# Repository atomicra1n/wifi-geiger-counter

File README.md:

# Wi-Fi Geiger Counter

A DIY Geiger counter PCB which can detect ionizing radiation and log readings over Wi-Fi. Built with a Raspberry Pi Pico 2 W, and a HV multiplier circuit that steps up 3.7V to 400V for the GM tube. Made THT to be easily buildable.

## Features

- M4011/SBM-20 Geiger tube with pulse detection (tuned for M4011)
- Custom HV circuit (around 400V) with a single LiPo cell
- Wi-Fi data logging with a dashboard and a JSON API
- Piezo buzzer with clicking on each count
- Battery charging via the Pico's Micro-USB port
- Power switch
- Fully THT with parts from my local electronic shop (GM Electronic)

## Motivation
I made this project as I already own a FNIRSI GC-01 Geiger Counter, but I've always been intrigued by how they work and wanted to have a crack at making my own. It was an interesting challenge, especially given the difficulties around handling 400 volts, clearance, etc. Additionally, given the addition of Wi-Fi compared to the GC-01, I can log data from anywhere (the GC-01 requires a constant USB-C connection).

## Functionality
- Power from the Pico's Micro-USB goes through the VBUS to a TP4056 charger module which charges the battery. 
- Pico uses PWM on a MPSA42 transistor which switches an inductor, it ramps up to 200V-ish and then a diode + capacitor voltage doubler ups that to around 400V.
- A 40Megaohm/220kiloohm resistor divider reduces the 400V down to around 2.19, which is read by the Pico via its ADC and PID in the firmware adjusts to continuously hold at 400V.
- When the M4011 tube detects decay, the pulse enters a transistor and it is turned into a 3.3V signal for the Pico which is counted and clicks the buzzer.
- The firmware tallies counts over 60 seconds to calculate a CPM and converts into micro Sv/h via the configured conversion factor. Pico hosts a small web page and a JSON endpoint.

## How it was made
This is my first project in KiCad, so I had to figure it out for the most part. I picked the parts on LCSC and imported them, sketched the HV circuit on paper and then built it step by step. A few issues I ran into:
- I configured net class patterns to keep HV clearance, but I misconfigured them (set to HV instead of /HV) and they were ignored. As such, when I thought I was done, none of my rules were actually checked.
- My USB TVS diode was wired the wrong way which would short VBUS. I swapped it for a bidirectional one.
- My status LED was backwards and improperly wired, so I changed it to stay high on boot.
- The USB-C connector was facing inside the board instead of outside, very easy mistake to make in the PCB editor! Had to rotate and reroute completely.
- The buzzer footprint didn't match my actual part, so I had to find the right one on LCSC and reimport it.
- The ADC reading was wrong by around 30% in the firmware, so I fixed it by using the calibrated ADC reading in MicroPython

### v2 (THT)
After my project got approved, I realized it was practically unbuildable, as the ESP32 had pads underneath and everything was tiny SMD, which for a beginner solderer like me was straight up impossible. As I had no hot air or hot plate (I only have a Pinecil), I redesigned it to be THT from my local retailer, which even saved some costs.

## Tech stack
- KiCad for the PCB design
- MicroPython for the Pico firmware
- JLCPCB for the board and GM Electronic for parts

## Repo layout
- pcb/ contains the actual KiCad project
- pcb/gerbers contain the gerber and drill files
- pcb/lib/ contains my custom footprints
- firmware/ contains the MicroPython code
- images/ contains a render of the PCB and other images
- BOM.csv contains the parts list
- JOURNAL.md is the devlog

## Bill of materials

| Part | Qty | Source | Unit | Total |
|---|---|---|---|---|
| [PCB Manufacturing](https://jlcpcb.com) | 1 | JLCPCB | $4.00 | $4.00 |
| [RASPBERRY Pico 2 WH](https://www.gme.cz/v/1517388/raspberry-pico-2-wh) | 1 | GM Electronic | $11.97 | $11.97 |
| [CONNFLY BL120G-V8.5 female header 1x20pin](https://www.gme.cz/v/1498892/connfly-bl120g-v85-dutinkova-lista-1x20pin-roztec-254mm-vyska-85mm) | 2 | GM Electronic | $0.44 | $0.88 |
| [CREATALL CA-033M TP4056 charger module](https://www.gme.cz/v/1518943/creatall-ca-033m-nabijecka-li-ion-clanku-tp4056-s-ochranou-microusb) | 1 | GM Electronic | $0.88 | $0.88 |
| [SEMTECH MPSA42 transistor](https://www.gme.cz/v/1485978/semtech-mpsa42-b-p-bipolarni-tranzistor) | 8 | GM Electronic | $0.13 | $1.04 |
| [FASTRON 09P-103J inductor 10mH](https://www.gme.cz/v/1487059/fastron-09p-103j-tlumivka) | 1 | GM Electronic | $0.91 | $0.91 |
| [HER108 diode](https://www.gme.cz/v/1493669/her108-dioda) | 12 | GM Electronic | $0.09 | $1.08 |
| [WIMA MKS4 10n/1500V](https://www.gme.cz/v/1491351/wima-mks4-10n-1500v-k-rm15-foliovy-kondenzator) | 3 | GM Electronic | $0.67 | $2.01 |
| [1N5819 Schottky](https://www.gme.cz/v/1493662/1n5819-schottkyho-dioda) | 6 | GM Electronic | $0.14 | $0.84 |
| [Resistor 1 kiloohm 0207](https://www.gme.cz/v/1486228/gym-cym-rm-1k-06w-1-0207-metalizovany-rezistor) | 10 | GM Electronic | $0.10 | $1.00 |
| [Resistor 10 kiloohm 0207](https://www.gme.cz/v/1494150/gym-cym-rm-10k-06w-1-0207-metalizovany-rezistor) | 10 | GM Electronic | $0.10 | $1.00 |
| [Resistor 100 kiloohm 0207](https://www.gme.cz/v/1494147/gym-cym-rm-100k-06w-1-0207-metalizovany-rezistor) | 10 | GM Electronic | $0.10 | $1.00 |
| [Resistor 220 kiloohm 0207](https://www.gme.cz/v/1493098/gym-cym-rm-220k-06w-1-0207-metalizovany-rezistor) | 10 | GM Electronic | $0.10 | $1.00 |
| [Resistor 4.7 megaohm 0207](https://www.gme.cz/v/1493090/gym-cym-rm-4m7-06w-1-0207-metalizovany-rezistor) | 10 | GM Electronic | $0.10 | $1.00 |
| [Resistor 10 megaohm 0207](https://www.gme.cz/v/1494151/gym-cym-rm-10m-06w-1-0207-metalizovany-rezistor) | 10 | GM Electronic | $0.10 | $1.00 |
| [GYM/CYM CK 100n/63V](https://www.gme.cz/v/1489722/gym-cym-ck-100n-63v-x7r-rm508-20-keramicky-kondenzator) | 4 | GM Electronic | $0.18 | $0.72 |
| [HITANO CE 220u/16V 8x12](https://www.gme.cz/v/1485860/hitano-ce-220u-16vit-hit-exr-8x12-rm35-bulk-elektrolyticky-kondenzator) | 5 | GM Electronic | $0.15 | $0.75 |
| [BRIGHT LED BL-B5141-L red](https://www.gme.cz/v/1492965/bright-led-bl-b5141-l-led-3mm-cervena) | 1 | GM Electronic | $0.17 | $0.17 |
| [HITPOINT PT-2040PQ piezo](https://www.gme.cz/v/1496868/hitpoint-pt-2040pq-piezomenic) | 1 | GM Electronic | $0.84 | $0.84 |
| [MTS-102-A2 toggle](https://www.gme.cz/v/1501004/mts-102-a2-packovy-spinac) | 1 | GM Electronic | $0.65 | $0.65 |
| [JST PH 2pin header](https://www.gme.cz/v/1517850/jst-ph-20mm-2pin-konektor-na-dps) | 2 | GM Electronic | $0.11 | $0.22 |
| [JST PH 3pin cable](https://www.gme.cz/v/1517846/jst-ph-20mm-3pin-samice) | 2 | GM Electronic | $0.37 | $0.74 |
| [KSS KDA6M3X15W standoff](https://www.gme.cz/v/1483417/kss-kda6m3x15w-polyamid-bily-distancni-sloupek-15mm-m3-matka-sroub) | 4 | GM Electronic | $0.23 | $0.92 |
| [WURTH SKM3K nut M3](https://www.gme.cz/v/1511808/wurth-skm3k-matice-m3) | 4 | GM Electronic | $0.03 | $0.12 |
| [KSS CV-100 zip tie](https://www.gme.cz/v/1512662/kss-cv-100-stahovaci-pasek) | 8 | GM Electronic | $0.03 | $0.24 |
| [GM Tube - M4011](https://github.com/SensorsIot/Geiger-Counter-RadiationD-v1.1-CAJOE-/blob/master/M4011%20Geiger%20Tube%20Specification.pdf) | 1 | Salvaged (FNIRSI GC-01) | $0.01 | $0.01 |
| 3.7V LiPo battery | 1 | Salvaged (FNIRSI GC-01) | $0.01 | $0.01 |
| **Parts subtotal** | | | | **$35.00** |
| Shipping (estimate) | | | | $11.00 |
| **Total** | | | | **$46.00** |

The Geiger Tube and Battery were salvaged from my GC-01, so they're effectively free. You can buy similar pieces on Ebay, Aliexpress or other stores.

## Assembly
Please keep in mind the board makes around 400V, even though it's low current, it could still inflict a shock, as such, please be careful. Before touching the HV side, I recommend unplugging the USB and battery and shorting C10 to GND to discharge it.

1. Order the PCB from JLCPCB using the gerber files and the parts from GM using the BOM.
2. Start with the power section. Put a piece of electrical tape where the TP4056 module goes, zip tie the module on and wire its 6 pads to J2 following the silkscreen labels. Then solder D1, C1 (polarity!), C2, SW1 and the J1 battery connector. Check battery polarity before plugging in or you might kill it! If you turn on SW1, you should get the battery voltage (4Vish) on VSYS.
3. Solder the Pico sockets, led + R30, buzzer. Plug in the RPi with the usb port facing the left edge of the PCB. Flash Micropython.
4. Begin the HV supply. Solder Q1, R10, R11, L1, D3-D5, C8-C10, divider chain R13-R16, R12, C11, R23. Do not connect the tube yet. Run the firmware and see how much HV you get. Do not measure with a multimeter to avoid loading the circuit.
5. Now for the pulse detection, solder Q2, R24, R25 and R26.
6. To finish, zip tie your tube onto J3 and solder leads. VERIFY ANODE AND CATHODE! Screw in the four standoffs and connect the battery.

## Firmware

1. Start by downloading MicroPython for the Pico 2 W from [micropython.org](https://micropython.org/download/RPI_PICO2_W/). Hold the BOOTSEL button on the Pico while plugging in and drag the .uf2 onto the drive that shows up.
2. Fill in firmware/config.py.
3. Copy over files: config.py, geiger.py, hv_control.py, buzzer.py, wifi_manager.py, main.py.
4. If all goes well, your IP address should get printed over serial. Try opening it in the browser for the dashboard, or use /api/data for the JSON data.

## AI disclosure
LLMs (Claude Opus 4.6/5.5) was mostly used to get feedback on the schematic, review parts of it, assist in fixing bugs and writing the dashboard in wifi_manager.py. It was also used for other tedious but simple tasks, such as adding the BOM to this README.

---

Built for [Hack Club Half Life](https://halflife.hackclub.com/) 
Week 1 (PCBs).

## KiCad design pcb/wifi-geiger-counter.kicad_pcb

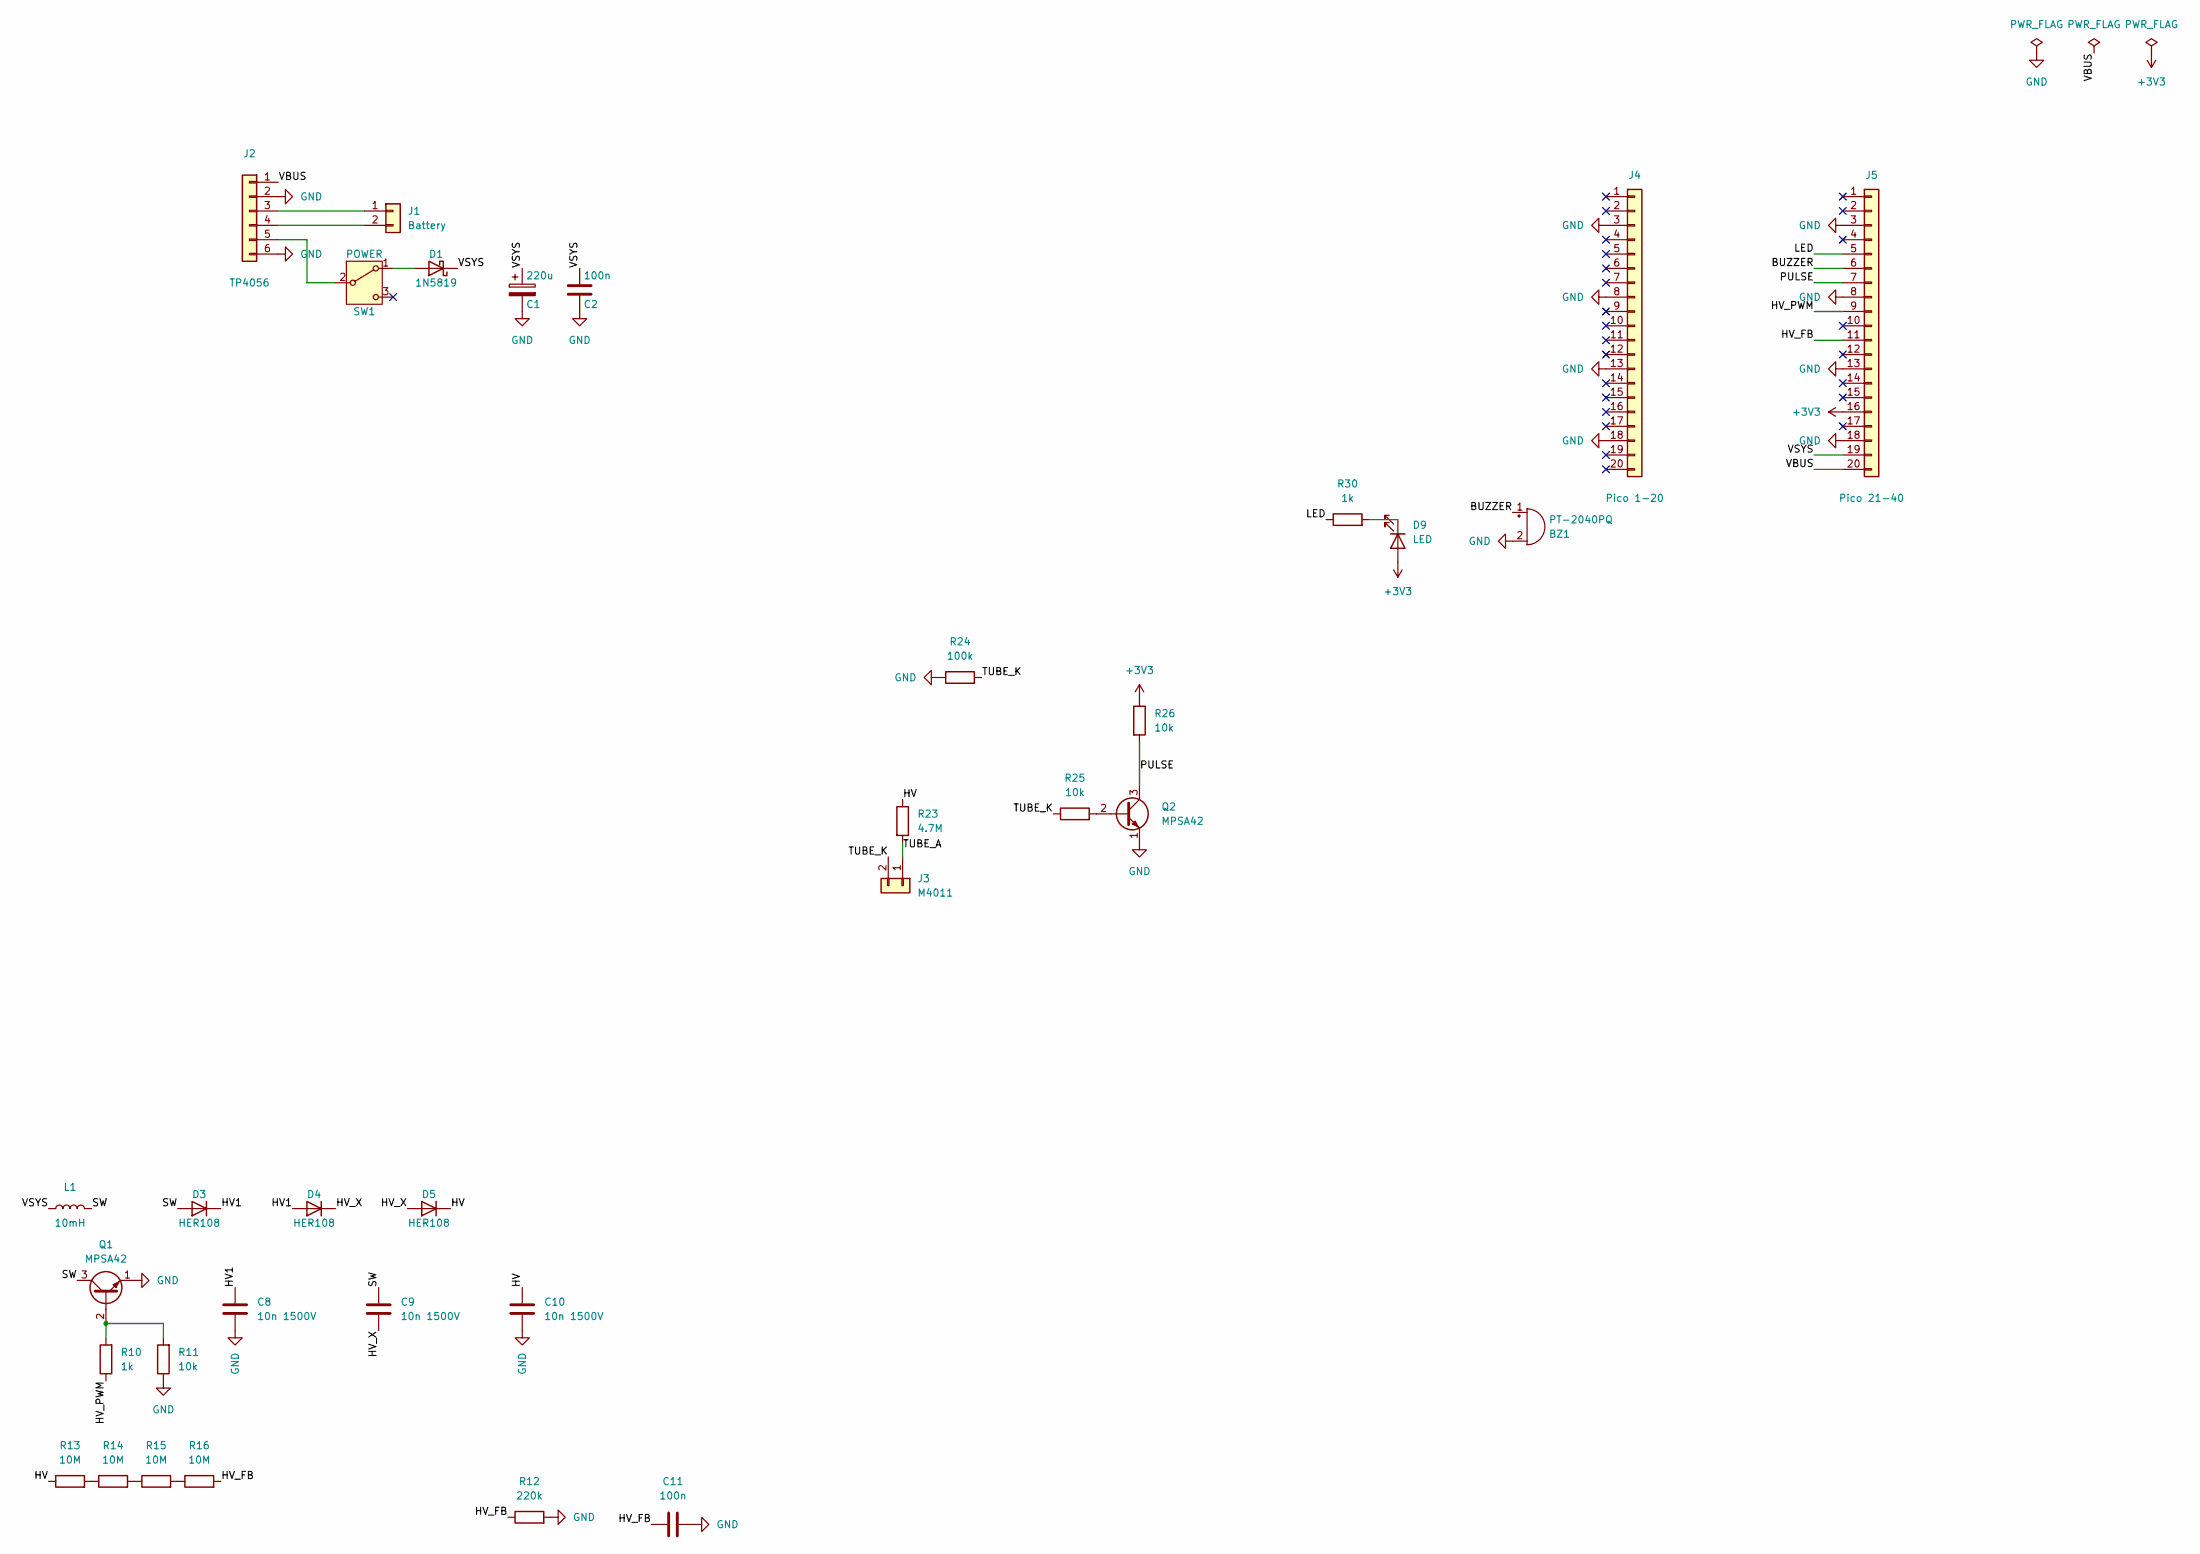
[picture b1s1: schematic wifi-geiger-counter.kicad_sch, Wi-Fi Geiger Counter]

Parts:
BZ1: PT-2040PQ; buzzer_2040pq
C1: 220u; CP_Radial_D8.0mm_P3.50mm
C2, C11: 100n; C_Disc_D5.0mm_W2.5mm_P5.00mm
C8, C9, C10: 10n 1500V; C_Rect_L18.0mm_W5.0mm_P15.00mm_FKS3_FKP3
D1: 1N5819; D_DO-41_SOD81_P10.16mm_Horizontal
D3, D4, D5: HER108; D_DO-41_SOD81_P10.16mm_Horizontal
D9: LED; LED_D3.0mm
J1: Battery; JST_PH_B2B-PH-K_1x02_P2.00mm_Vertical
J2: TP4056
J3: M4011; tube
J4: Pico 1-20; PinSocket_1x20_P2.54mm_Vertical
J5: Pico 21-40; PinSocket_1x20_P2.54mm_Vertical
L1: 10mH; L_Radial_D10.0mm_P5.00mm_Fastron_07P
Q1, Q2: MPSA42; TO-92_Inline_Wide
R10, R30: 1k; R_Axial_DIN0207_L6.3mm_D2.5mm_P10.16mm_Horizontal
R11, R25, R26: 10k; R_Axial_DIN0207_L6.3mm_D2.5mm_P10.16mm_Horizontal
R12: 220k; R_Axial_DIN0207_L6.3mm_D2.5mm_P10.16mm_Horizontal
R13, R14, R15, R16: 10M; R_Axial_DIN0207_L6.3mm_D2.5mm_P10.16mm_Horizontal
R23: 4.7M; R_Axial_DIN0207_L6.3mm_D2.5mm_P10.16mm_Horizontal
R24: 100k; R_Axial_DIN0207_L6.3mm_D2.5mm_P10.16mm_Horizontal
SW1: POWER; SW_MTS-102-A2

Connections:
+3V3: D9.2 (A), J5.16, R26.1
/BUZZER: BZ1.1 (+), J5.6
/HV: C10.1, D5.1 (K), R13.1, R23.1
/HV1: C8.1, D3.1 (K), D4.2 (A)
/HV_FB: C11.1, J5.11, R12.1, R16.2
/HV_PWM: J5.9, R10.1
/HV_X: C9.2, D4.1 (K), D5.2 (A)
/LED: J5.5, R30.1
/PULSE: J5.7, Q2.3 (C), R26.2
/SW: C9.1, D3.2 (A), L1.2, Q1.3 (C)
/TUBE_A: J3.1, R23.2
/TUBE_K: J3.2, R24.2, R25.1
/VBUS: J2.1, J5.20
/VSYS: C1.1, C2.1, D1.1 (K), J5.19, L1.1
GND: BZ1.2 (-), C1.2, C2.2, C8.2, C10.2, C11.2, J2.2, J2.6, J4.3, J4.8, J4.13, J4.18, J5.3, J5.8, J5.13, J5.18, Q1.1 (E), Q2.1 (E), R11.1, R12.2, R24.1
unnamed: D1.2 (A), SW1.1 (A)
unnamed: D9.1 (K), R30.2
unnamed: J1.1, J2.3
unnamed: J1.2, J2.4
unnamed: J2.5, SW1.2 (B)
unnamed: Q1.2 (B), R10.2, R11.2
unnamed: Q2.2 (B), R25.2
unnamed: R13.2, R14.1
unnamed: R14.2, R15.1
unnamed: R15.2, R16.1

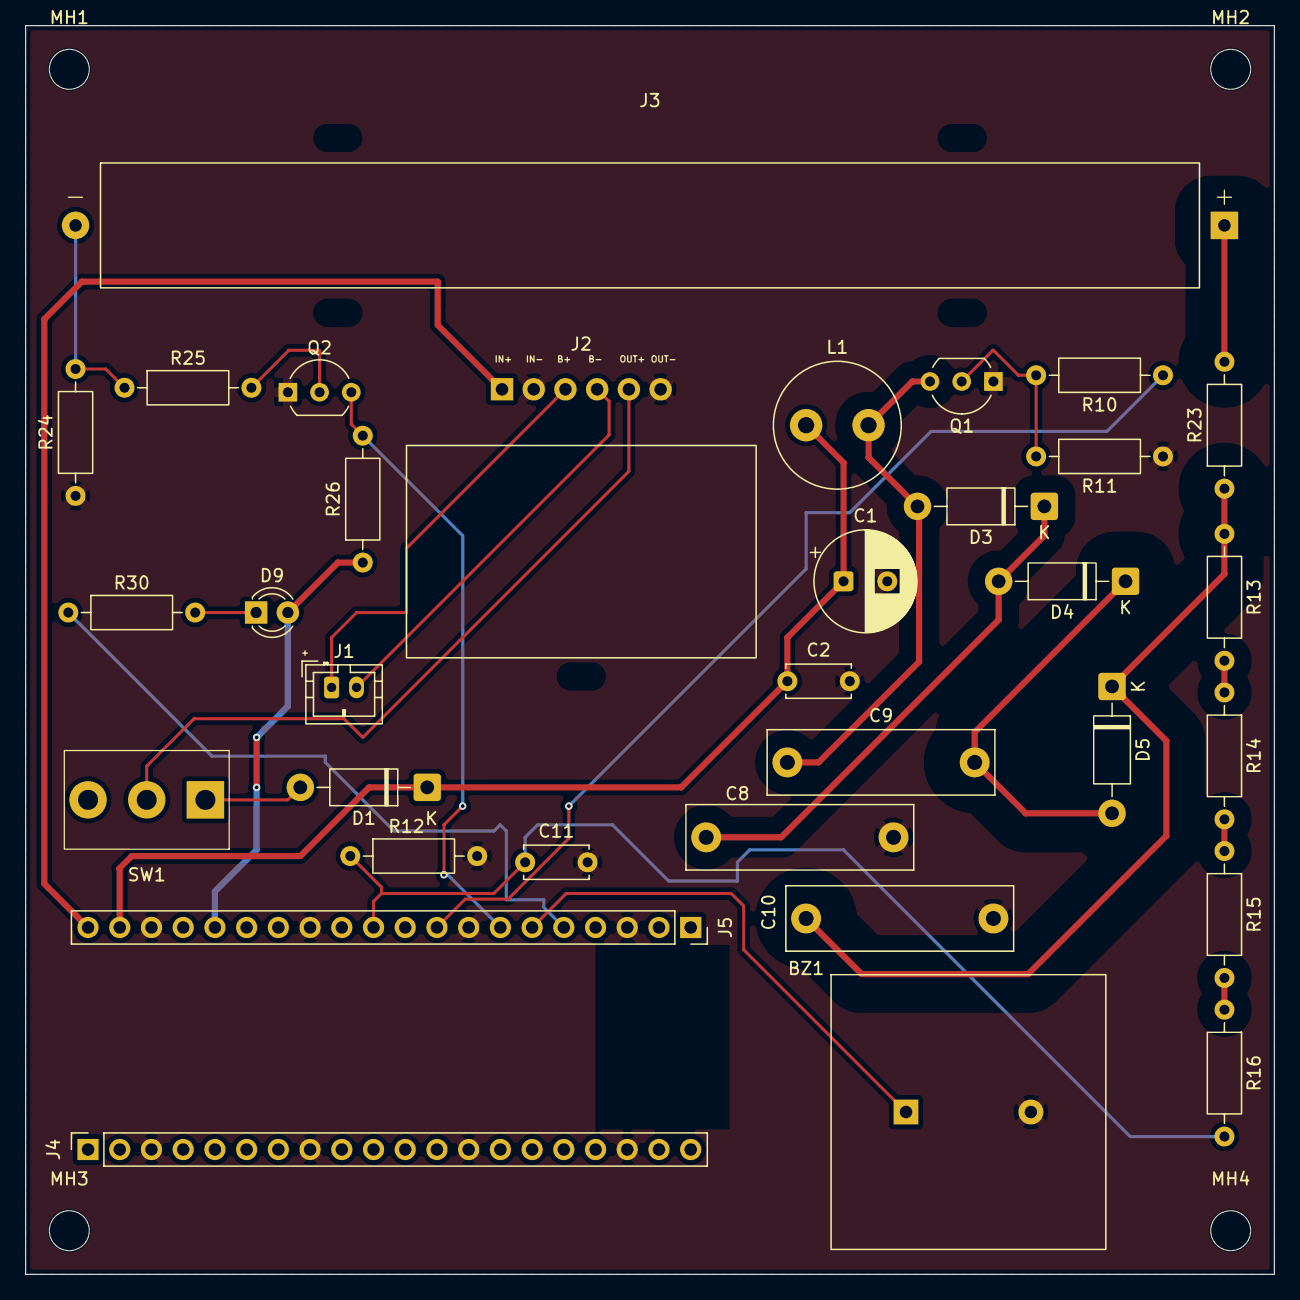
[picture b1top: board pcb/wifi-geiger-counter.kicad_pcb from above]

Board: 2 copper layers, 100.0 x 100.0 mm, 37 parts (0 on the bottom side), 25 nets.

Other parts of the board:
MH1, MH2, MH3, MH4: MountingHole_3.2mm_M3

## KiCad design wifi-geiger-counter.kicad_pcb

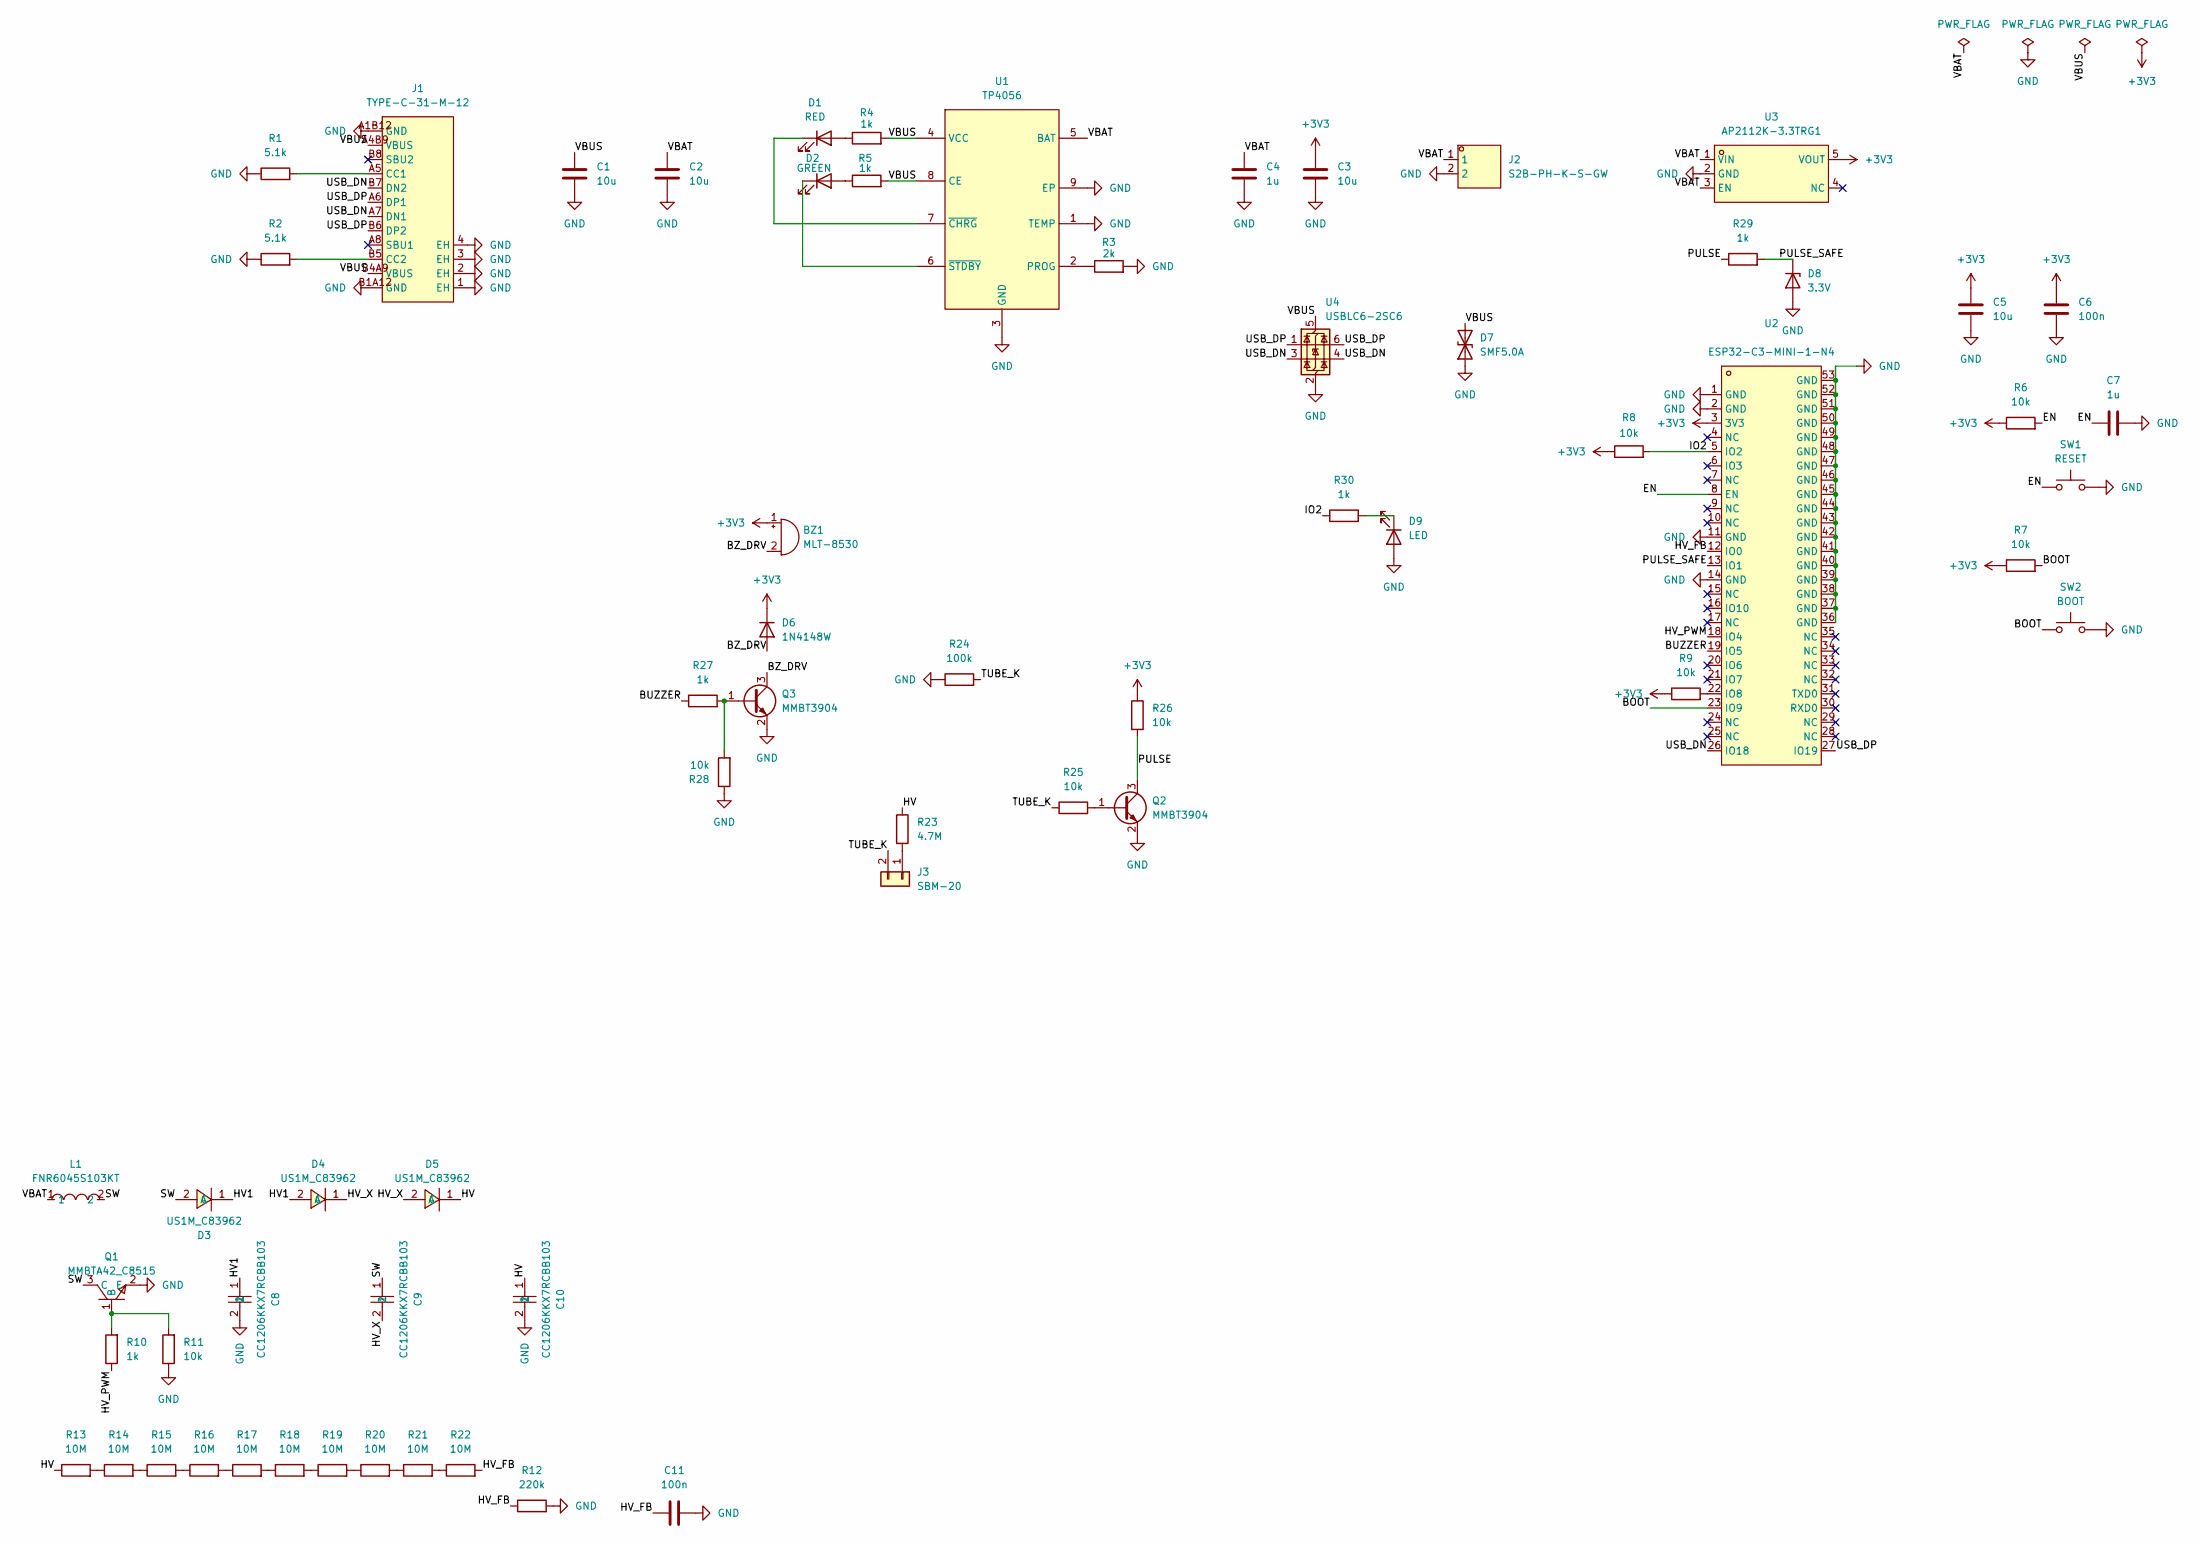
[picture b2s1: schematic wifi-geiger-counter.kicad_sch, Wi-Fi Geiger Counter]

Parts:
BZ1: MLT-8530; Buzzer_Murata_PKMCS0909E
C1, C2, C3, C5: 10u; C_0805_2012Metric
C4, C7: 1u; C_0805_2012Metric
C6, C11: 100n; C_0805_2012Metric
C8, C9, C10: CC1206KKX7RCBB103; C1206; MPN CC1206KKX7RCBB103; LCSC Part C107192
D1: RED; LED_0805_2012Metric
D2: GREEN; LED_0805_2012Metric
D3, D4, D5: US1M_C83962; SMA_L4.3-W2.6-LS5.2-RD; MPN US1M; LCSC Part C83962
D6: 1N4148W; D_SOD-123
D7: SMF5.0A; D_SOD-123F
D8: 3.3V; D_SOD-323
D9: LED; LED_0805_2012Metric
J1: TYPE-C-31-M-12; USB-C_SMD-TYPE-C-31-M-12_1; MPN TYPE-C-31-M-12; LCSC Part C165948
J2: S2B-PH-K-S-GW; CONN-TH_S2B-PH-K-S-GW; MPN S2B-PH-K-S-GW; LCSC Part C157932
J3: SBM-20; PinHeader_1x02_P2.54mm_Vertical
L1: FNR6045S103KT; IND-SMD_L6.0-W6.0_FNR60XXS; MPN FNR6045S103KT; LCSC Part C168108
Q1: MMBTA42_C8515; SOT-23-3_L2.9-W1.3-P1.90-LS2.4-BR; MPN MMBTA42(RANGE:100-200); LCSC Part C8515
Q2, Q3: MMBT3904; SOT-23
R1, R2: 5.1k; R_0805_2012Metric
R3: 2k; R_0805_2012Metric
R4, R5, R10, R27, R29, R30: 1k; R_0805_2012Metric
R6, R7, R8, R9, R11, R25, R26, R28: 10k; R_0805_2012Metric
R12: 220k; R_0805_2012Metric
R13, R14, R15, R16, R17, R18, R19, R20, R21, R22: 10M; R_1206_3216Metric
R23: 4.7M; R_1206_3216Metric
R24: 100k; R_0805_2012Metric
SW1: RESET; SW_SPST_CK_KMS2xxGP
SW2: BOOT; SW_SPST_CK_KMS2xxGP
U1: TP4056; ESOP-8_L4.9-W3.9-P1.27-LS6.0-BL-EP; MPN TP4056-42-ESOP8; LCSC Part C16581
U2: ESP32-C3-MINI-1-N4; WIFIM-SMD_ESP32-C3-MINI-1; MPN ESP32-C3-MINI-1-N4; LCSC Part C2838502
U3: AP2112K-3.3TRG1; SOT-25-5_L2.9-W1.6-P0.95-LS2.8-BL; MPN AP2112K-3.3TRG1; LCSC Part C51118
U4: USBLC6-2SC6; SOT-23-6

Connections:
+3V3: BZ1.1 (+), C3.1, C5.1, C6.1, D6.1 (K), R6.1, R7.1, R8.1, R9.1, R26.1, U2.3 (3V3), U3.5 (VOUT)
/BOOT: R7.2, SW2.1, U2.23 (IO9)
/BUZZER: R27.1, U2.19 (IO5)
/BZ_DRV: BZ1.2 (-), D6.2 (A), Q3.3 (C)
/EN: C7.2, R6.2, SW1.1, U2.8 (EN)
/HV: C10.1, D5.1 (C), R13.1, R23.1
/HV1: C8.1, D3.1 (C), D4.2 (A)
/HV_FB: C11.1, R12.1, R22.2, U2.12 (IO0)
/HV_PWM: R10.1, U2.18 (IO4)
/HV_X: C9.2, D4.1 (C), D5.2 (A)
/IO2: R8.2, R30.1, U2.5 (IO2)
/PULSE: Q2.3 (C), R26.2, R29.1
/PULSE_SAFE: D8.1 (K), R29.2, U2.13 (IO1)
/SW: C9.1, D3.2 (A), L1.2, Q1.3 (C)
/TUBE_K: J3.2, R24.2, R25.1
/USB_DN: J1.A7 (DN1), J1.B7 (DN2), U2.26 (IO18), U4.3 (I/O2), U4.4 (I/O2)
/USB_DP: J1.A6 (DP1), J1.B6 (DP2), U2.27 (IO19), U4.1 (I/O1), U4.6 (I/O1)
/VBAT: C2.1, C4.1, J2.1, L1.1, U1.5 (BAT), U3.1 (VIN), U3.3 (EN)
/VBUS: C1.2, D7.2 (A2), J1.A4B9 (VBUS), J1.B4A9 (VBUS), R4.2, R5.2, U1.4 (VCC), U1.8 (CE), U4.5 (VBUS)
GND: C1.1, C2.2, C3.2, C4.2, C5.2, C6.2, C7.1, C8.2, C10.2, C11.2, D7.1 (A1), D8.2 (A), D9.2 (A), J1.1 (EH), J1.2 (EH), J1.3 (EH), J1.4 (EH), J1.A1B12 (GND), J1.B1A12 (GND), J2.2, Q1.2 (E), Q2.2 (E), Q3.2 (E), R1.1, R2.1, R3.2, R11.1, R12.2, R24.1, R28.1, SW1.2, SW2.2, U1.1 (TEMP), U1.3 (GND), U1.9 (EP), U2.1 (GND), U2.2 (GND), U2.11 (GND), U2.14 (GND), U2.36 (GND), U2.37 (GND), U2.38 (GND), U2.39 (GND), U2.40 (GND), U2.41 (GND), U2.42 (GND), U2.43 (GND), U2.44 (GND), U2.45 (GND), U2.46 (GND), U2.47 (GND), U2.48 (GND), U2.49 (GND), U2.50 (GND), U2.51 (GND), U2.52 (GND), U2.53 (GND), U3.2 (GND), U4.2 (GND)
unnamed: D1.2 (A), R4.1
unnamed: D1.1 (K), U1.7 (~CHRG)
unnamed: D2.2 (A), R5.1
unnamed: D2.1 (K), U1.6 (~STDBY)
unnamed: D9.1 (K), R30.2
unnamed: J1.A5 (CC1), R1.2
unnamed: J1.B5 (CC2), R2.2
unnamed: J3.1, R23.2
unnamed: Q1.1 (B), R10.2, R11.2
unnamed: Q2.1 (B), R25.2
unnamed: Q3.1 (B), R27.2, R28.2
unnamed: R13.2, R14.1
unnamed: R14.2, R15.1
unnamed: R15.2, R16.1
unnamed: R16.2, R17.1
unnamed: R17.2, R18.1
unnamed: R18.2, R19.1
unnamed: R19.2, R20.1
unnamed: R20.2, R21.1
unnamed: R21.2, R22.1
unnamed: R3.1, U1.2 (PROG)
unnamed: R9.2, U2.22 (IO8)

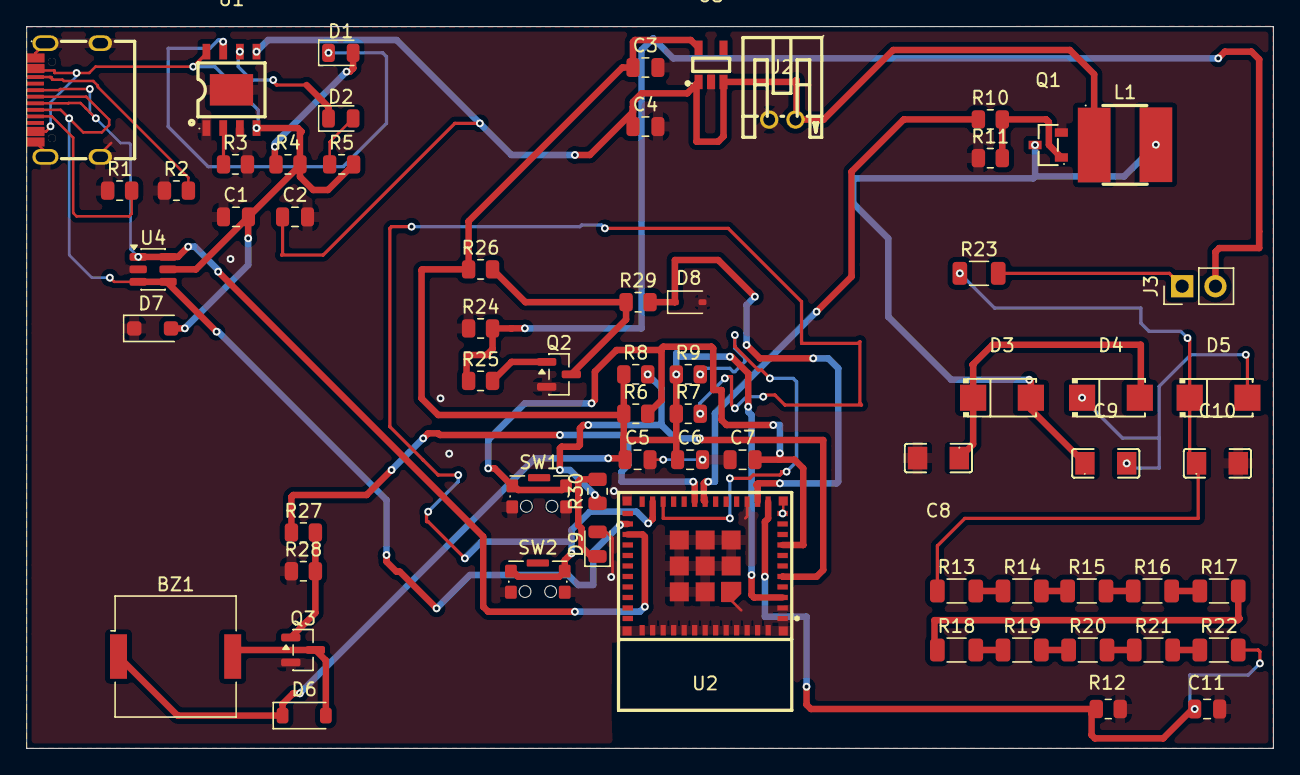
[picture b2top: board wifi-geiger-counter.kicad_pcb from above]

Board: 2 copper layers, 95.0 x 55.0 mm, 64 parts (0 on the bottom side), 42 nets.

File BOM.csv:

Item,Qty,Supplier,Cost/item,Total Cost,link
PCB Manufacturing,1,JLCPCB,$4.00,$4.00,https://jlcpcb.com
EPS32-C3-MINI,1,LCSC,$3.06,$3.06,https://www.lcsc.com/product-detail/C2838502.html
TP4056-42-ESOP8,5,LCSC,$0.19,$0.95,https://www.lcsc.com/product-detail/C16581.html
AP2112K-3.3TRG1,5,LCSC,$0.18,$0.90,https://www.lcsc.com/product-detail/C51118.html
USBLC6-2SC6,5,LCSC,$0.18,$0.90,https://www.lcsc.com/product-detail/C7519.html
MMBTA42,10,LCSC,$0.05,$0.50,https://www.lcsc.com/product-detail/C94389.html
MMBT3904,20,LCSC,$0.04,$0.80,https://www.lcsc.com/product-detail/C242260.html
US1M,3,LCSC,$0.05,$0.15,https://www.lcsc.com/product-detail/C81191.html
1N4148W,50,LCSC,$0.01,$0.50,https://www.lcsc.com/product-detail/C917030.html
SMF5.0A,5,LCSC,$0.13,$0.65,https://www.lcsc.com/product-detail/C151296.html
MM3Z3V3,50,LCSC,$0.02,$1.00,https://www.lcsc.com/product-detail/C52056.html
Red LED 0805,50,LCSC,$0.02,$1.00,https://www.lcsc.com/product-detail/C84256.html
Yellow LED 0805,20,LCSC,$0.02,$0.40,https://www.lcsc.com/product-detail/C84261.html
MLT-8530,5,LCSC,$0.21,$1.05,https://www.lcsc.com/product-detail/C94599.html
FNR6045S103KT,5,LCSC,$0.25,$1.25,https://www.lcsc.com/product-detail/C168108.html
TYPE-C-31-M-12,5,LCSC,$0.18,$0.90,https://www.lcsc.com/product-detail/C165948.html
S2B-PH-K-S-GW,5,LCSC,$0.17,$0.85,https://www.lcsc.com/product-detail/C157932.html
1k 0805,100,LCSC,$0.01,$1.00,https://www.lcsc.com/product-detail/C17513.html
10k 0805,100,LCSC,$0.01,$1.00,https://www.lcsc.com/product-detail/C17414.html
5.1k 0805,100,LCSC,$0.01,$1.00,https://www.lcsc.com/product-detail/C27834.html
2.2k 0805,100,LCSC,$0.01,$1.00,https://www.lcsc.com/product-detail/C17520.html
220k 0805,100,LCSC,$0.01,$1.00,https://www.lcsc.com/product-detail/C17556.html
100k 0805,100,LCSC,$0.01,$1.00,https://www.lcsc.com/product-detail/C17407.html
4.7M 1206 500V,10,LCSC,$0.01,$0.10,https://www.lcsc.com/product-detail/C510138.html
10M 1206,100,LCSC,$0.01,$1.00,https://www.lcsc.com/product-detail/C2933576.html
10µF 0805,20,LCSC,$0.07,$1.40,https://www.lcsc.com/product-detail/C15850.html
1µF 0805,10,LCSC,$0.04,$0.40,https://www.lcsc.com/product-detail/C28323.html
100nF 0805,20,LCSC,$0.02,$0.40,https://www.lcsc.com/product-detail/C49678.html
10nF 1kV 1206,20,LCSC,$0.03,$0.60,https://www.lcsc.com/product-detail/C107192.html
Tact switch,20,LCSC,$0.02,$0.40,https://www.lcsc.com/product-detail/C318884.html
GM Tube - M4011,1,Myself - Salvaged from FNIRSI GC-01,$0.01,$0.01,https://github.com/SensorsIot/Geiger-Counter-RadiationD-v1.1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
3.7V LiPo battery,1,Myself - Salvaged from FNIRSI GC-01,$0.01,$0.01,https://tipa.eu/en-en/products/rechargeable-battery-lipo-3-7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
2.54-1*3P,20,LCSC,$0.03,$0.60,https://www.lcsc.com/product-detail/C49257.html
Estimated total shipping,1,,,$25.00,

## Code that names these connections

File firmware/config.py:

# pin assignments
HV_PWM_PIN = 22
HV_FB_PIN = 26 
PULSE_PIN = 21
BUZZER_PIN = 20
LED_PIN = 19

# the feedback divider is 40M/220k so ratio is like 182.8
# 400v / 182.8 = 2.19v = 2190mv on the adc
HV_TARGET = 2190

# m4011 tube conversion factor
CPM_TO_USVH = 0.0066

WIFI_SSID = ""
WIFI_PASS = ""
